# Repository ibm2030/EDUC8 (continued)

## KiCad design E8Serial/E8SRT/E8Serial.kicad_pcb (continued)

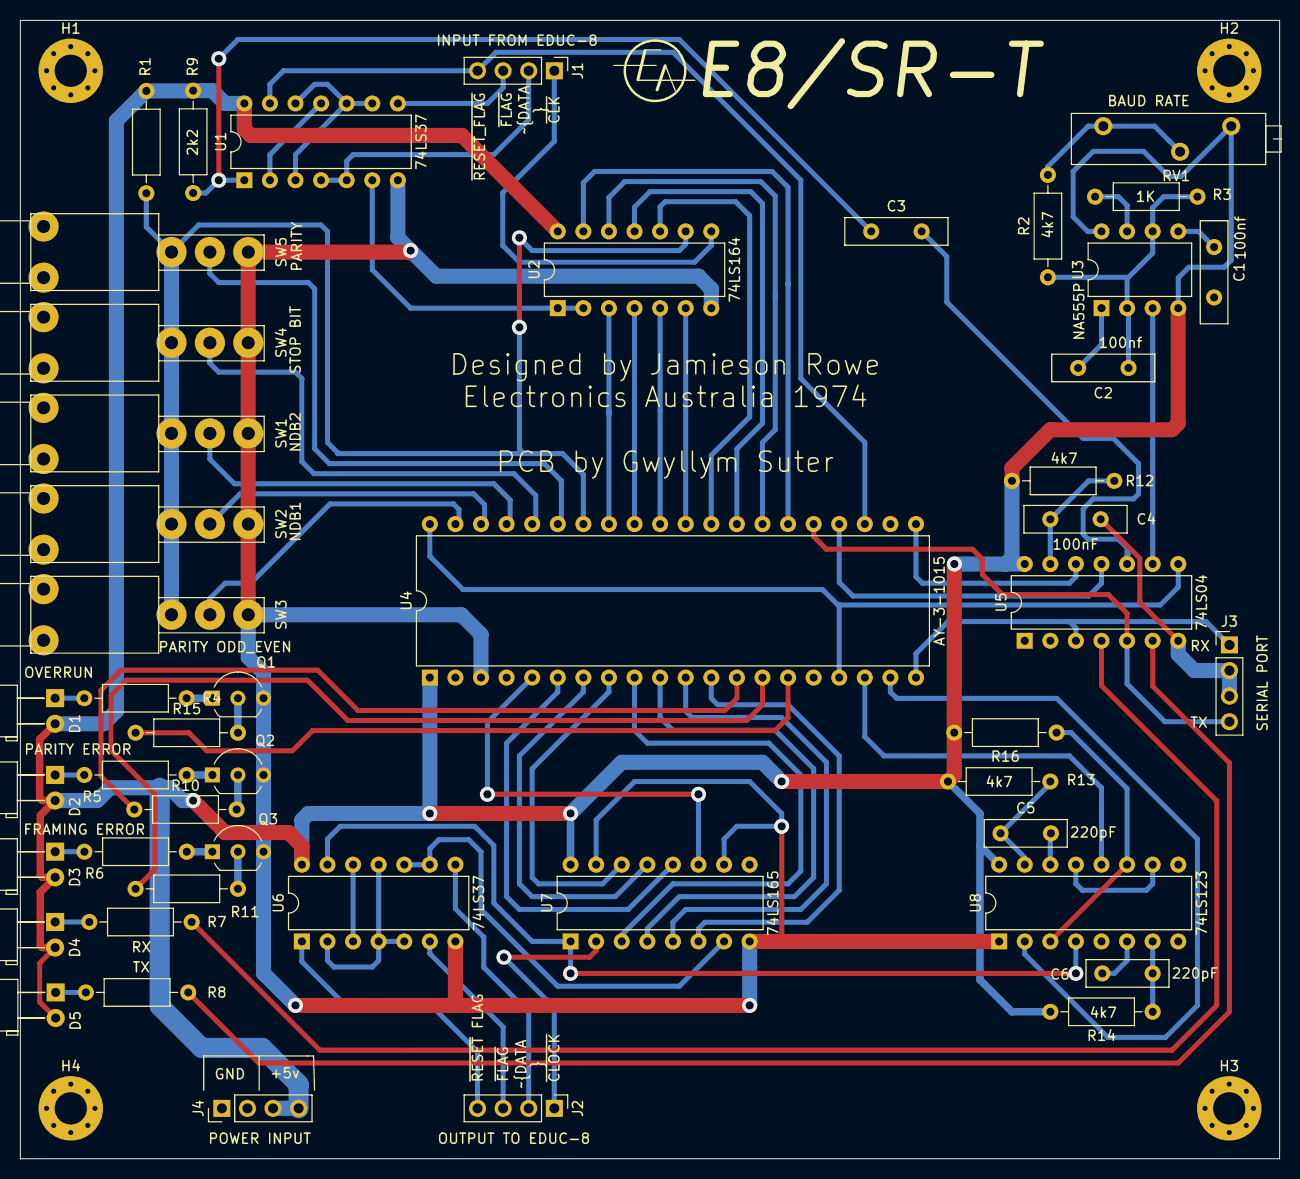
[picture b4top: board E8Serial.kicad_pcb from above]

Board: 2 copper layers, 125.0 x 113.0 mm, 52 parts (0 on the bottom side), 76 nets.

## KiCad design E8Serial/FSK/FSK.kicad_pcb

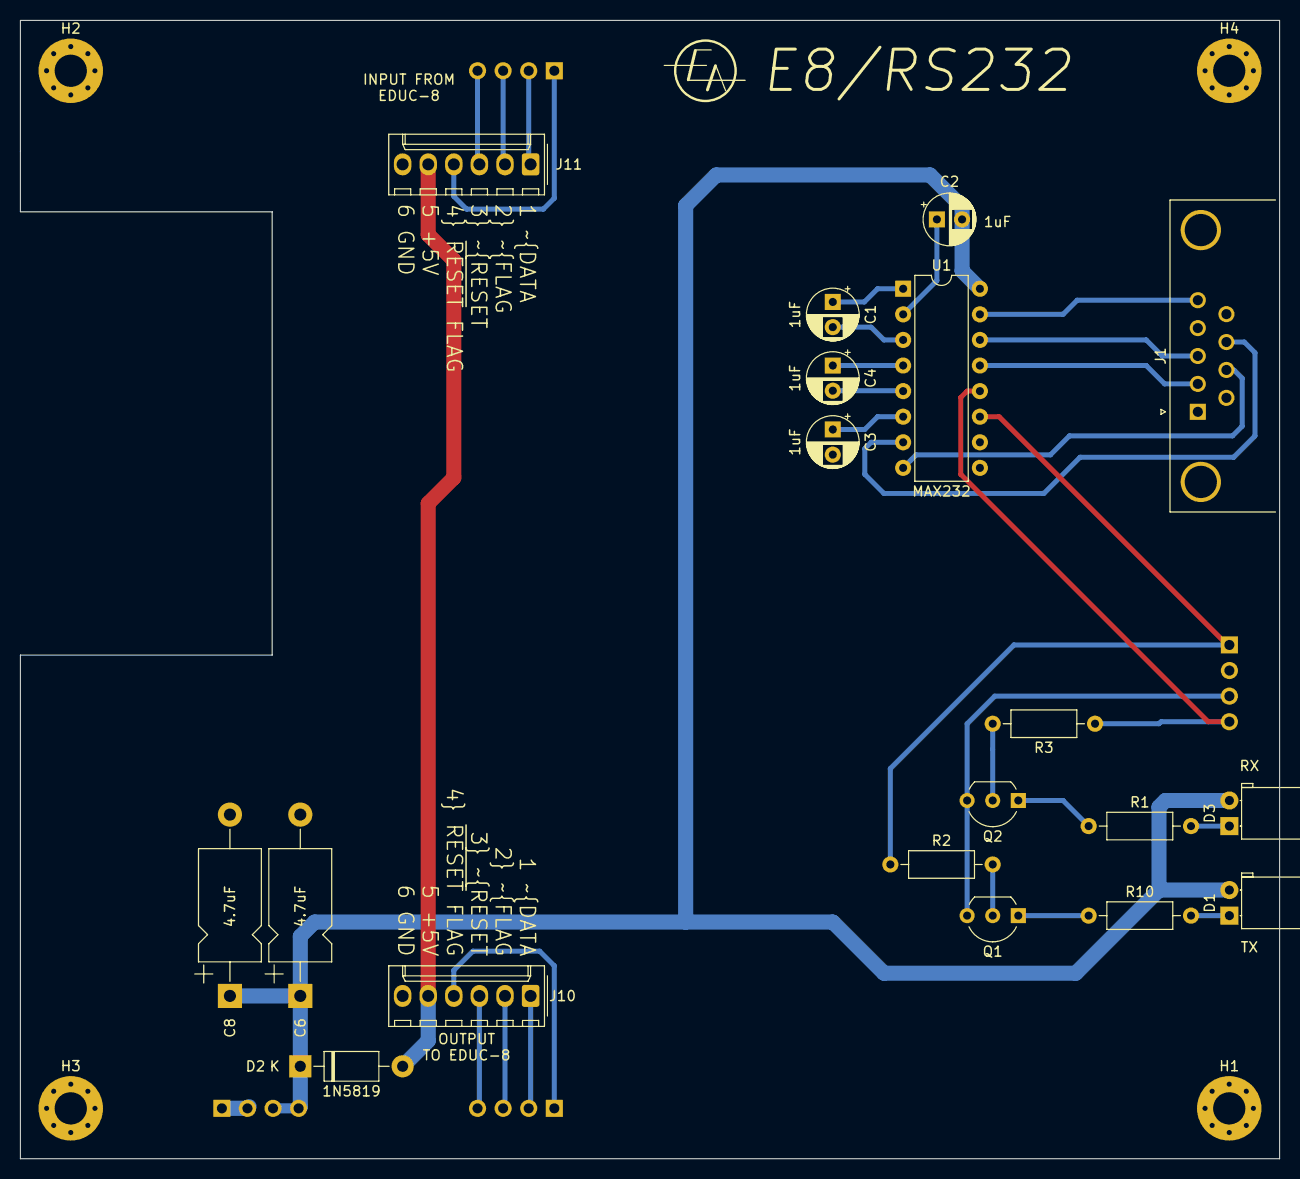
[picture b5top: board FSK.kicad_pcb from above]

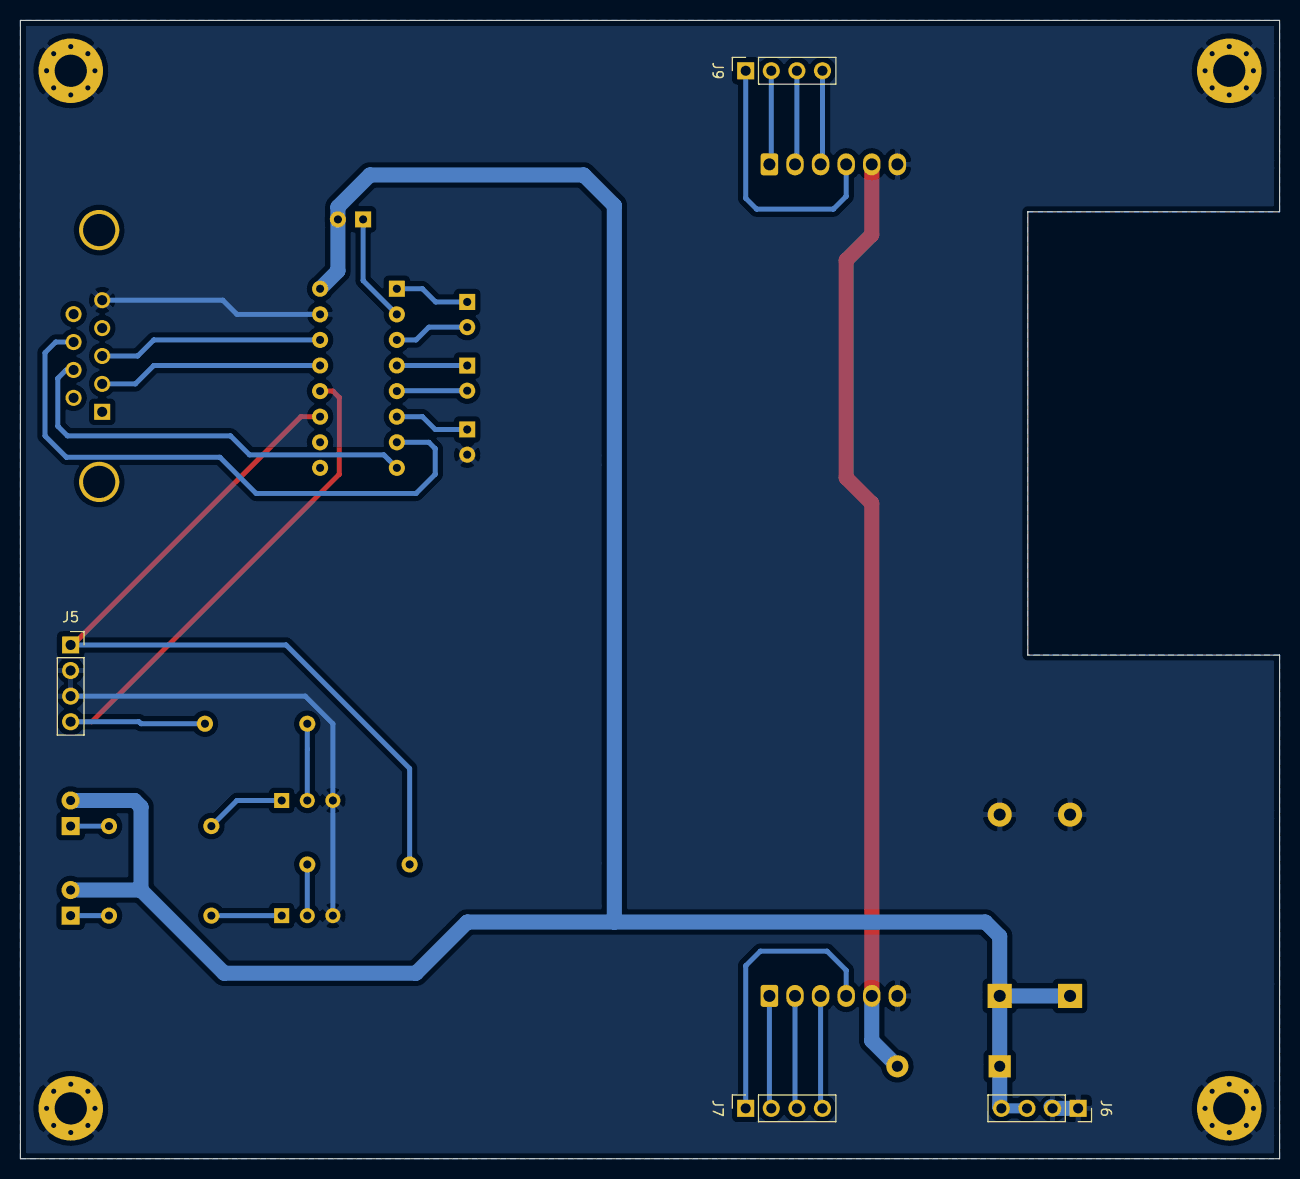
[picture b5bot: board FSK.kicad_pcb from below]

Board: 2 copper layers, 125.0 x 113.0 mm, 27 parts (4 on the bottom side), 29 nets.

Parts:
C1, C2, C3, C4: 1uF; CP_Radial_D5.0mm_P2.50mm
C6, C8: 4.7uF; CP_Axial_L11.0mm_D6.0mm_P18.00mm_Horizontal
D1, D3: LED; LED_D5.0mm_Horizontal_O1.27mm_Z3.0mm
D2: 1N5819; D_DO-41_SOD81_P10.16mm_Horizontal
H1, H2, H3, H4: M3; MountingHole_3.2mm_M3_Pad_Via
J1: DB9_Male; DSUB-9_Male_Horizontal_P2.77x2.84mm_EdgePinOffset4.94mm_Hou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
J5, J6, J7, J9: Conn_01x04_Female; PinSocket_1x04_P2.54mm_Vertical
J10, J11: Conn_01x06_Male; Molex_KK-254_AE-6410-06A_1x06_P2.54mm_Vertical
Q1, Q2: BC548; TO-92_Inline_Wide
R1, R10: 180R; R_Axial_DIN0207_L6.3mm_D2.5mm_P10.16mm_Horizontal
R2, R3: 4k7; R_Axial_DIN0207_L6.3mm_D2.5mm_P10.16mm_Horizontal
U1: MAX232; DIP-16_W7.62mm

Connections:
+5V: C2.2, C6.1, C8.1, D1.2, D2.1, D3.2, J6.3, J6.4, U1.16
CTS: J1.8, U1.7
GND: C3.2, C6.2, C8.2, H1.1, H2.1, H3.1, H4.1, J1.5, J5.2, J5.3, J6.1, J6.2, J10.6, J11.6, Q1.3, Q2.3, U1.15
I_clock: J7.1, J10.4
I_data: J7.2, J10.1
I_flag: J7.3, J10.2
I_rst: J7.4, J10.3
unnamed: C1.1, U1.1
unnamed: C1.2, U1.3
unnamed: C2.1, U1.2
unnamed: C3.1, U1.6
unnamed: C4.1, U1.4
unnamed: C4.2, U1.5
unnamed: D1.1, R10.2
unnamed: D2.2, J10.5, J11.5
unnamed: D3.1, R1.2
unnamed: Q1.1, R10.1
unnamed: Q1.2, R2.2
unnamed: Q2.1, R1.1
unnamed: Q2.2, R3.2
RTS: J1.7, U1.8
RX: J5.4, R3.1
RX_D: J1.2, U1.13
TX: J5.1, R2.1, U1.11
TX_D: J1.3, U1.14
clock: J9.1, J11.4
data: J9.2, J11.1
flag: J9.3, J11.2
rst: J9.4, J11.3

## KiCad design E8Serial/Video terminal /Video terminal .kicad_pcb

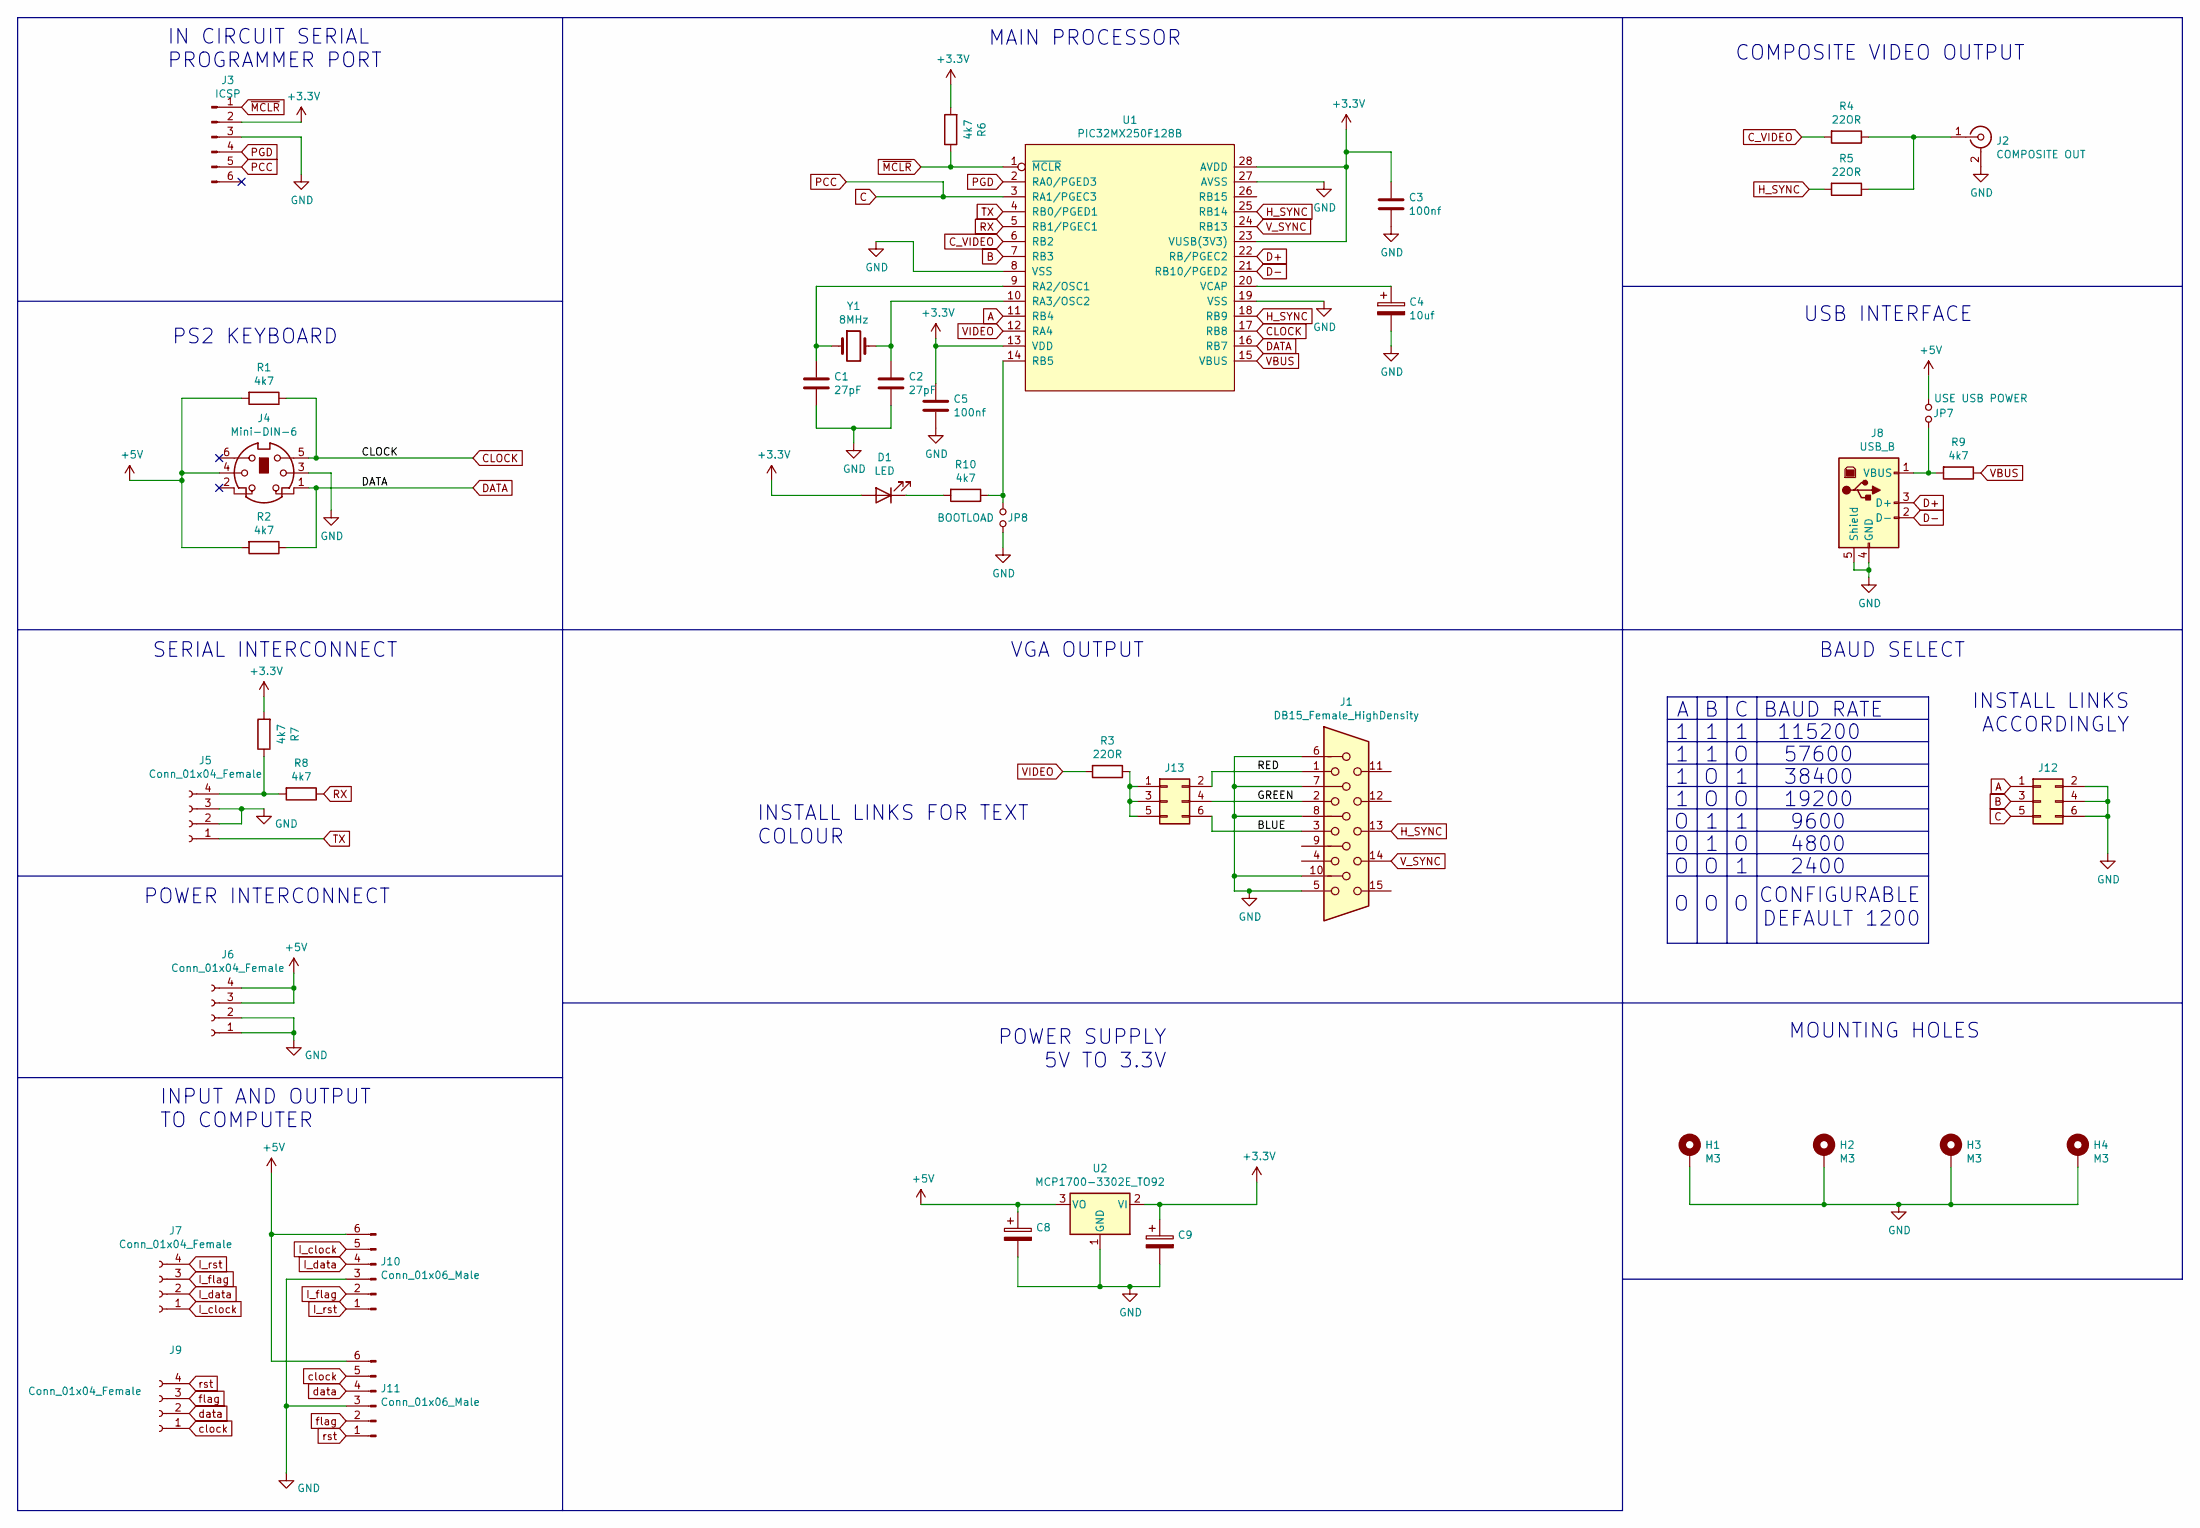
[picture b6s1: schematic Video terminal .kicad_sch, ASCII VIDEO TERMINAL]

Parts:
C1, C2: 27pF; C_Disc_D4.3mm_W1.9mm_P5.00mm
C3, C5: 100nf; C_Rect_L7.0mm_W3.5mm_P5.00mm
C4: 10uf; CP_Radial_D5.0mm_P2.50mm
C8, C9: CP_Radial_D6.3mm_P2.50mm
D1: LED; LED_D5.0mm_Horizontal_O1.27mm_Z3.0mm
H1, H2, H3, H4: M3; MountingHole_3.2mm_M3_Pad_Via
J1: DB15_Female_HighDensity; DSUB-15-HD_Female_Horizontal_P2.29x1.98mm_EdgePinOffset3.03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
J2: COMPOSITE OUT; BNC_Amphenol_031-6575_Horizontal
J3: ICSP; PinHeader_1x06_P2.54mm_Vertical
J4: Mini-DIN-6; 6_pin_mini_din
J5, J6, J7, J9: Conn_01x04_Female; PinSocket_1x04_P2.54mm_Vertical
J8: USB_B; USB_B_Lumberg_2411_02_Horizontal
J10, J11: Conn_01x06_Male; Molex_KK-254_AE-6410-06A_1x06_P2.54mm_Vertical
J12, J13: Conn_02x03_Odd_Even; PinHeader_2x03_P2.54mm_Vertical
JP7: USE USB POWER; PinHeader_2x01_P2.54mm_Vertical
JP8: BOOTLOAD; PinHeader_2x01_P2.54mm_Vertical
R1, R2, R6, R7, R8, R9, R10: 4k7; R_Axial_DIN0207_L6.3mm_D2.5mm_P10.16mm_Horizontal
R3, R4, R5: 22OR; R_Axial_DIN0207_L6.3mm_D2.5mm_P10.16mm_Horizontal
U1: PIC32MX250F128B; DIP-28_W7.62mm
U2: MCP1700-3302E_TO92; TO-92_Inline_Wide
Y1: 8MHz; Crystal_HC49-4H_Vertical

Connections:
+3V3: C3.1, C5.1, C9.1, D1.2 (A), J3.2, R6.2, R7.2, U1.13 (VDD), U1.23 (VUSB(3V3)), U1.28 (AVDD), U2.2 (VI)
+5V: C8.1, J4.4, J6.3, J6.4, J10.6, J11.6, JP7.1, R1.2, R2.2, U2.3 (VO)
/BLUE: J1.3, J13.6
/GREEN: J1.2, J13.4
/RED: J1.1, J13.2
A: J12.1, U1.11 (RB4)
B: J12.3, U1.7 (RB3)
C: J3.5, J12.5, U1.3 (RA1/PGEC3)
CLOCK: J4.5, R1.1, U1.17 (RB8)
C_VIDEO: R4.2, U1.6 (RB2)
D+: J8.3 (D+), U1.22 (RB/PGEC2)
D-: J8.2 (D-), U1.21 (RB10/PGED2)
DATA: J4.1, R2.1, U1.16 (RB7)
GND: C1.2, C2.2, C3.2, C4.2, C5.2, C8.2, C9.2, H1.1, H2.1, H3.1, H4.1, J1.5, J1.6, J1.7, J1.8, J1.10, J2.2 (Ext), J3.3, J4.3, J5.2, J5.3, J6.1, J6.2, J8.4 (GND), J8.5 (Shield), J10.3, J11.3, J12.2, J12.4, J12.6, JP8.2, U1.8 (VSS), U1.19 (VSS), U1.27 (AVSS), U2.1 (GND)
H_SYNC: J1.13, R5.2, U1.18 (RB9), U1.25 (RB14)
I_clock: J7.1, J10.5
I_data: J7.2, J10.4
I_flag: J7.3, J10.2
I_rst: J7.4, J10.1
unnamed: C1.1, U1.9 (RA2/OSC1), Y1.1
unnamed: C2.1, U1.10 (RA3/OSC2), Y1.2
unnamed: C4.1, U1.20 (VCAP)
unnamed: D1.1 (K), R10.2
unnamed: J2.1 (In), R4.1, R5.1
unnamed: J5.4, R7.1, R8.2
unnamed: J8.1 (VBUS), JP7.2, R9.2
unnamed: J13.1, J13.3, J13.5, R3.1
unnamed: JP8.1, R10.1, U1.14 (RB5)
PGD: J3.4, U1.2 (RA0/PGED3)
RX: R8.1, U1.5 (RB1/PGEC1)
TX: J5.1, U1.4 (RB0/PGED1)
VBUS: R9.1, U1.15 (VBUS)
VIDEO: R3.2, U1.12 (RA4)
V_SYNC: J1.14, U1.24 (RB13)
clock: J9.1, J11.5
data: J9.2, J11.4
flag: J9.3, J11.2
rst: J9.4, J11.1
~MCLR: J3.1, R6.1, U1.1 (~MCLR)

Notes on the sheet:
MAIN PROCESSOR
BAUD SELECT
38400
115200
4800
COMPOSITE VIDEO OUTPUT
INSTALL LINKS ACCORDINGLY
9600
2400
IN CIRCUIT SERIAL PROGRAMMER PORT
INSTALL LINKS FOR TEXT COLOUR
POWER SUPPLY 5V TO 3.3V
SERIAL INTERCONNECT
POWER INTERCONNECT
USB INTERFACE
19200
57600
PS2 KEYBOARD
INPUT AND OUTPUT TO COMPUTER
MOUNTING HOLES
CONFIGURABLE DEFAULT 1200
VGA OUTPUT
BAUD RATE

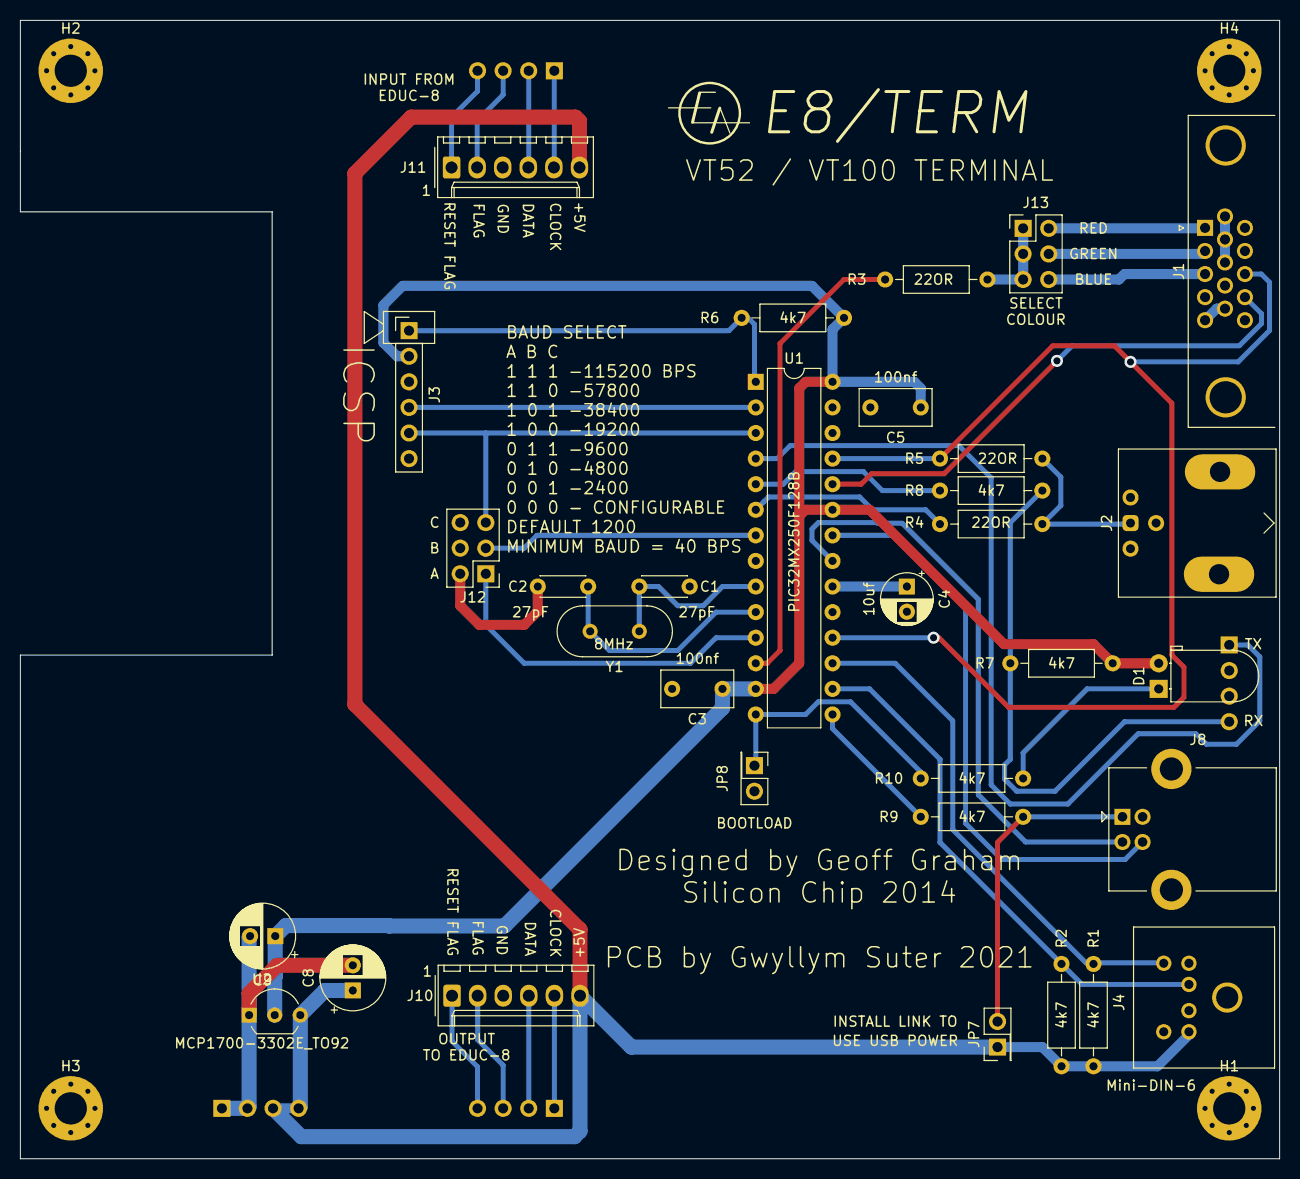
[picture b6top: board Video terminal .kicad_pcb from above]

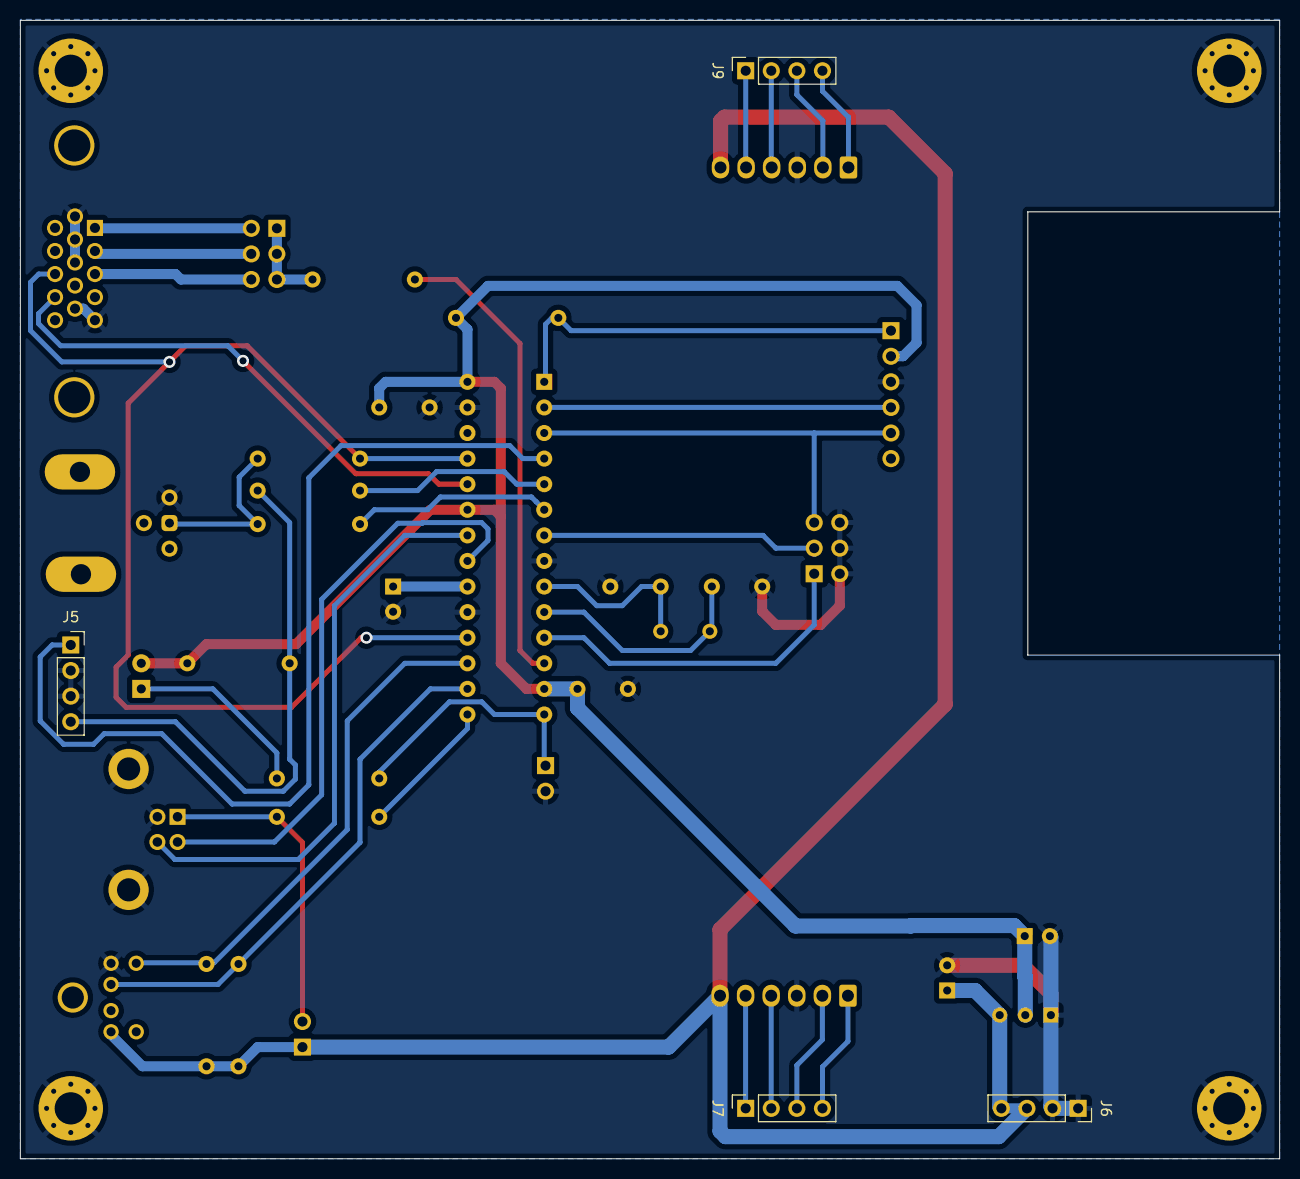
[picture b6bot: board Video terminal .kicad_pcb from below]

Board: 2 copper layers, 125.0 x 113.0 mm, 40 parts (4 on the bottom side), 39 nets.
